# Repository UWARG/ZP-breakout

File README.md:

# ZP-breakout
Breakout Board for Zeropilot rev 1.0.

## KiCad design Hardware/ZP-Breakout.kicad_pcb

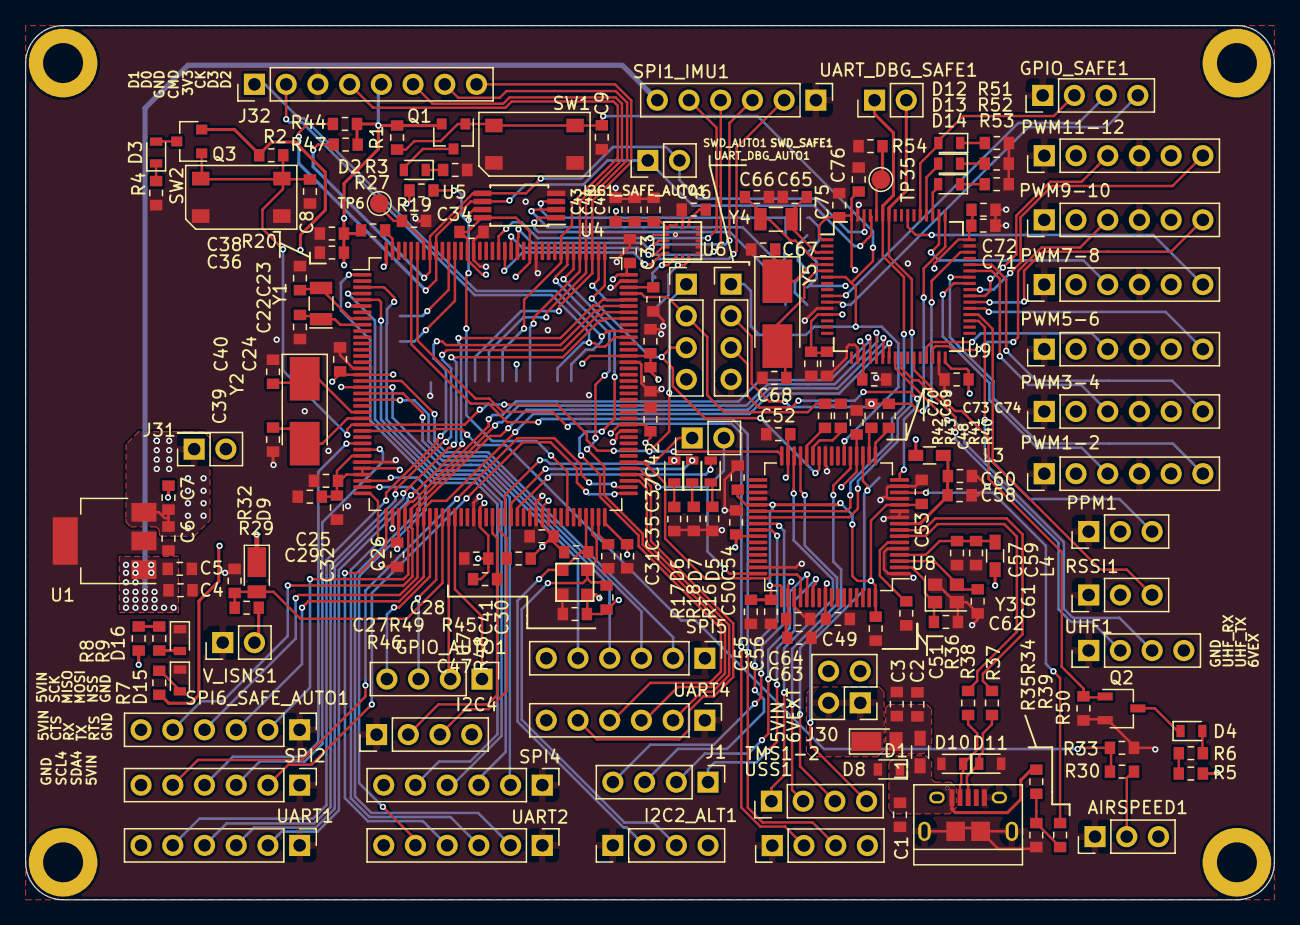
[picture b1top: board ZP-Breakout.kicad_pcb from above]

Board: 4 copper layers, 100.0 x 70.0 mm, 193 parts (0 on the bottom side), 160 nets.

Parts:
AIRSPEED1: GH-3; PinHeader_1x03_P2.54mm_Vertical
C1, C2, C43, C69: 10nF; C_0603_1608Metric_Pad0.84x1.00mm_HandSolder
C3, C4, C38, C59, C60, C63, C72, C76: 4.7uF; C_0603_1608Metric_Pad0.84x1.00mm_HandSolder
C5, C6, C32, C37, C70: 1uF; C_0603_1608Metric_Pad0.84x1.00mm_HandSolder
C7, C8, C9, C24, C25, C26, C27, C28, C29, C30, C31, C33, C34, C35, C36, C44, C46, C47, C48, C49, C50, C51, C52, C53, C54, C55, C57, C58, C64, C71, C73, C74, C75: 100nF; C_0603_1608Metric_Pad0.84x1.00mm_HandSolder
C22, C23, C65, C66: 14pF; C_0603_1608Metric_Pad0.84x1.00mm_HandSolder
C39, C40, C67, C68: 7pF; C_0603_1608Metric_Pad0.84x1.00mm_HandSolder
C41, C42, C45: 2.2uF; C_0603_1608Metric_Pad0.84x1.00mm_HandSolder
C56: 3.3uF; C_0603_1608Metric_Pad0.84x1.00mm_HandSolder
C61, C62: 8pF; C_0603_1608Metric_Pad0.84x1.00mm_HandSolder
D1, D10, D11: TVS; D_0603_1608Metric_Pad0.67x1.00mm_HandSolder
D2, D3, D5, D6, D7, D12, D13, D14: LED; LED_0603_1608Metric_Pad0.67x1.00mm_HandSolder
D4, D15, D16: PWR_LED; LED_0603_1608Metric_Pad0.67x1.00mm_HandSolder
D8, D9: D; D_PowerDI-123
GPIO_AUTO1: GH-4; PinHeader_1x04_P2.54mm_Vertical
GPIO_SAFE1: GH-4; PinHeader_1x04_P2.54mm_Vertical
H1, H2, H3, H4: MountingHole_M3; MountingHole_3.2mm_M3_ISO14580_Pad
I2C1_SAFE_AUTO1: GH-2; PinHeader_1x02_P2.54mm_Vertical
I2C2_ALT1, I2C4: GH-4; PinHeader_1x04_P2.54mm_Vertical
J1: GH-4; PinHeader_1x04_P2.54mm_Vertical
J8: Micro_SD_Card; micro_sd
J9: USB_MICRO_B; USB_Micro-B_10118194-0001LF
J30: Conn_02x02_Odd_Even; PinSocket_2x02_P2.54mm_Vertical
J31: Conn_01x02; PinSocket_2x01_P2.54mm_Vertical
J32: CONN-8; PinHeader_1x08_P2.54mm_Vertical
L1: BLM18PG221SN1D; L_0603_HandSoldering
L3, L4: 600R; L_0603_HandSoldering
PPM1: GH-3; PinHeader_1x03_P2.54mm_Vertical
PWM1-2, PWM3-4, PWM5-6, PWM7-8, PWM9-10, PWM11-12: GH-6; PinHeader_1x06_P2.54mm_Vertical
Q1, Q3: BSS84LT1G; SOT-23
Q2: BSS138; TSOT-23
R1, R2, R19, R22, R24, R26, R27, R35, R44, R45, R46, R47, R48, R49, R54: 10K; R_0603_1608Metric_Pad0.84x1.00mm_HandSolder
R3, R4, R5, R6, R7, R8, R9, R16, R17, R18, R51, R52, R53: 100; R_0603_1608Metric_Pad0.84x1.00mm_HandSolder
R20, R21, R23, R25, R41, R42: 0; R_0603_1608Metric_Pad0.84x1.00mm_HandSolder
R29: 150K; R_0603_1608Metric_Pad0.84x1.00mm_HandSolder
R30: 11K; R_0603_1608Metric_Pad0.84x1.00mm_HandSolder
R32, R33: 22K; R_0603_1608Metric_Pad0.84x1.00mm_HandSolder
R34: 4.7K; R_0603_1608Metric_Pad0.84x1.00mm_HandSolder
R36: 12K; R_0603_1608Metric_Pad0.84x1.00mm_HandSolder
R37, R38: 10; R_0603_1608Metric_Pad0.84x1.00mm_HandSolder
R39: 1K; R_0603_1608Metric_Pad0.84x1.00mm_HandSolder
R40, R43: 220; R_0603_1608Metric_Pad0.84x1.00mm_HandSolder
R50: 100K; R_0603_1608Metric_Pad0.84x1.00mm_HandSolder
RSSI1: GH-3; PinHeader_1x03_P2.54mm_Vertical
SPI1_IMU1, SPI2, SPI4, SPI5, SPI6_SAFE_AUTO1: GH-6; PinHeader_1x06_P2.54mm_Vertical
SW1, SW2: SW_Push_Dual_1-2short_3-4short; Button
SWD_AUTO1: GH-4; PinHeader_1x04_P2.54mm_Vertical
SWD_SAFE1: GH-4; PinHeader_1x04_P2.54mm_Vertical
TMS1-2: GH-4; PinHeader_1x04_P2.54mm_Vertical
TP1, TP2, TP3, TP4, TP5, TP6, TP35: TEST; TestPoint_Pad_D1.5mm
U1: MCP1826S-3302E/DB; SOT-223
U4: STM32F765ZGT6; LQFP-144_20x20mm_P0.5mm
U5: M24C64-WDW6TP; TSSOP-8_4.4x3mm_P0.65mm
U6: ICM-20602
U7: MS5637-02BA03
U8: FT4232H; LQFP-64_10x10mm_P0.5mm
U9: STM32F091RCT7; LQFP-64_10x10mm_P0.5mm
UART1, UART2, UART4: GH-6; PinHeader_1x06_P2.54mm_Vertical
UART_DBG_AUTO1: GH-2; PinHeader_1x02_P2.54mm_Vertical
UART_DBG_SAFE1: GH-2; PinHeader_1x02_P2.54mm_Vertical
UHF1: GH-4; PinHeader_1x04_P2.54mm_Vertical
USS1: GH-4; PinHeader_1x04_P2.54mm_Vertical
V_ISNS1: GH-2; PinHeader_1x02_P2.54mm_Vertical
Y1, Y4: 32.768kHz; Crystal_SMD_MicroCrystal_CC7V-T1A-2Pin_3.2x1.5mm
Y2, Y5: 8MHz; Crystal_SMD_5032-2Pin_5.0x3.2mm_HandSoldering
Y3: Crystal_GND24; Crystal_SMD_2520-4Pin_2.5x2.0mm

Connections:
/3V3: C24.1, C25.1, C26.1, C27.1, C28.1, C29.1, C30.1, C31.1, C32.2, C33.1, C34.1, C35.1, C36.1, C37.2, C38.2, C43.2, C44.1, C45.1, C47.2, C48.1, C49.1, C50.1, C52.1, C63.1, C64.1, C69.1, C70.1, C71.1, C72.1, C73.1, C74.1, C75.1, C76.1, D9.1, J8.4, J31.2, J32.5, L3.2, L4.2, Q1.2, Q3.2, R1.2, R2.2, R7.1, R20.1, R21.1, R23.1, R25.1, R27.1, R44.1, R45.1, R46.1, R47.1, R48.1, R49.1, U4.6, U4.17, U4.30, U4.32, U4.33, U4.39, U4.52, U4.62, U4.72, U4.84, U4.95, U4.108, U4.121, U4.131, U4.144, U5.8, U6.1, U6.16, U7.1, U8.20, U8.31, U8.42, U8.50, U8.56, U9.1, U9.13, U9.19, U9.32, U9.48, U9.64
/5V_INT: AIRSPEED1.3, C4.2, C5.1, I2C2_ALT1.4, I2C4.4, J30.4, R5.1, R8.1, SPI1_IMU1.6, SPI2.6, SPI4.6, SPI5.6, SPI6_SAFE_AUTO1.6, U1.1, UART1.6, UART2.6, UART4.6, USS1.4
/5V_USB: C1.2, D1.1, J9.1, L1.1, R34.1
/6V_EXT: J30.2, PWM1-2.2, PWM1-2.5, PWM3-4.2, PWM3-4.5, PWM5-6.2, PWM5-6.5, PWM7-8.2, PWM7-8.5, PWM9-10.2, PWM9-10.5, PWM11-12.2, PWM11-12.5, UHF1.4
/AIRSPD_ADC: R30.1, R33.1, U4.26
/AIR_SPD: AIRSPEED1.2, R30.2
/CTS1: U4.103, UART1.5
/CTS2: U4.34, UART2.5
/CTS4: U4.76, UART4.5
/JRST: TP5.1, U4.134
/MEMORY/E1: R21.2, R22.1, U5.1
/MEMORY/E2: R23.2, R24.1, U5.2
/MEMORY/E3: R25.2, R26.1, U5.3
/MEM_WC: R27.2, U4.66, U5.7
/MISO1: SPI1_IMU1.4, U4.124, U6.4
/MISO2: SPI2.4, U4.28
/MISO4: SPI4.4, U4.4
/MISO5: SPI5.4, U4.20
/MISO6: SPI6_SAFE_AUTO1.4, U4.42, U9.22
/MOSI1: SPI1_IMU1.3, U4.123, U6.3
/MOSI2: SPI2.3, U4.29
/MOSI4: SPI4.3, U4.5
/MOSI5: SPI5.3, U4.21
/MOSI6: SPI6_SAFE_AUTO1.3, U4.43, U9.23
/NRST_PILOT: C8.1, Q3.1, R2.1, SW2.1, SW2.2, SWD_AUTO1.1, U4.25, U8.32
/NRST_SAFETY: C9.1, Q1.1, R1.1, SW1.1, SW1.2, SWD_SAFE1.1, U8.22, U9.7
/NSS1: SPI1_IMU1.2, U4.125, U6.5
/NSS2: SPI2.2, U4.73
/NSS4: SPI4.2, U4.3
/NSS5: SPI5.2, U4.18
/NSS6: SPI6_SAFE_AUTO1.2, U4.40, U9.20
/PB1: GPIO_AUTO1.2, U4.47
/PB2: GPIO_AUTO1.1, U4.48
/PC4: GPIO_AUTO1.4, U4.44
/PC5: GPIO_AUTO1.3, U4.45
/POWER/3V3_JMP: C6.1, C7.1, J31.1, U1.3
/POWER/5V_INT_JMP: D8.1, J30.1, J30.3
/PPM: PPM1.3, U9.35
/PWM 1-12/PWM1: PWM1-2.3, U9.41
/PWM 1-12/PWM2: PWM1-2.6, U9.42
/PWM 1-12/PWM3: PWM3-4.3, U9.43
/PWM 1-12/PWM4: PWM3-4.6, U9.44
/PWM 1-12/PWM5: PWM5-6.3, U9.29
/PWM 1-12/PWM6: PWM5-6.6, U9.37
/PWM 1-12/PWM7: PWM7-8.3, U9.50
/PWM 1-12/PWM8: PWM7-8.6, U9.55
/PWM 1-12/PWM9: PWM9-10.3, U9.30
/PWM 1-12/PWM10: PWM9-10.6, U9.38
/PWM 1-12/PWM11: PWM11-12.3, U9.39
/PWM 1-12/PWM12: PWM11-12.6, U9.40
/RSSI: RSSI1.3, U9.36
/RTS1: U4.104, UART1.2
/RTS2: U4.35, UART2.2
/RTS4: U4.75, UART4.2
/RX1: U4.102, UART1.4
/RX2: U4.37, UART2.4
/RX3: U4.78, U8.52, UART_DBG_AUTO1.1
/RX4: U4.114, UART4.4
/SAFETY_DBG_RX: U8.38, U9.59, UART_DBG_SAFE1.1
/SAFETY_DBG_TX: U8.39, U9.58, UART_DBG_SAFE1.2
/SCK1: SPI1_IMU1.5, U4.126, U6.2
/SCK2: SPI2.5, U4.74
/SCK4: SPI4.5, U4.1
/SCK5: SPI5.5, U4.19
/SCK6: SPI6_SAFE_AUTO1.5, U4.41, U9.21
/SCL1: I2C1_SAFE_AUTO1.1, R44.2, U4.136, U5.6, U9.61
/SCL2: I2C2_ALT1.2, R45.2, U4.69, U7.3
/SCL4: I2C4.2, R46.2, U4.54
/SCLK_PILOT: SWD_AUTO1.3, U4.109, U8.26
/SCLK_SAFETY: SWD_SAFE1.3, U8.16, U9.49
/SDA1: I2C1_SAFE_AUTO1.2, R47.2, U4.137, U5.5, U9.62
/SDA2: I2C2_ALT1.3, R48.2, U4.70, U7.2
/SDA4: I2C4.3, R49.2, U4.55
/SD_CK: J8.5, J32.6, U4.113
/SD_CMD: J8.3, J32.4, U4.116
/SD_D0: J8.7, J32.2, U4.98
/SD_D1: J8.8, J32.1, U4.99
/SD_D2: J8.1, J32.8, U4.111
/SD_D3: J8.2, J32.7, U4.112
/SENSORS/IMU_FSYNC: TP2.1, U6.8
/SENSORS/IMU_INT: TP1.1, U6.6
/SWIO_PILOT: R42.2, R43.2, SWD_AUTO1.2, U4.105
/SWIO_SAFETY: R40.2, R41.2, SWD_SAFE1.2, U9.46
/S_PC2: GPIO_SAFE1.3, U9.10
/S_PC3: GPIO_SAFE1.4, U9.11
/S_PC12: D12.2, GPIO_SAFE1.2, U9.53
/TDI: TP3.1, U4.110
/TDO: TP4.1, U4.133
/TDO1_TST: TMS1-2.4, U8.19
/TDO2_TST: TMS1-2.2, U8.29
/TMS1_TST: TMS1-2.3, U8.21
/TMS2_TST: TMS1-2.1, U8.30
/TX1: U4.101, UART1.3
/TX2: U4.36, UART2.3
/TX3: U4.77, U8.48, UART_DBG_AUTO1.2
/TX4: U4.115, UART4.3
/UART1_CTS_TST: J1.3, U8.41
/UART1_RTS_TST: J1.4, U8.40
/UART2_CTS_TST: J1.1, U8.54
/UART2_RTS_TST: J1.2, U8.53
/UHF_RX: U9.25, UHF1.2
/UHF_TX: U9.24, UHF1.3
/ULTRA_SONIC_1: U4.139, USS1.2
/ULTRA_SONIC_2: U4.140, USS1.3
/USB Interface/D+: R37.1, U8.8
/USB Interface/D-: R38.1, U8.7
/USB Interface/DR+: D11.1, J9.3, R37.2
/USB Interface/DR-: D10.1, J9.2, R38.2
/V_ISENSE: R29.2, V_ISNS1.2
/V_ISENSE_ADC: D9.2, R29.1, R32.1, U4.46
GND: AIRSPEED1.1, C1.1, C2.1, C3.1, C4.1, C5.2, C6.2, C7.2, C8.2, C9.2, C22.2, C23.2, C24.2, C25.2, C26.2, C27.2, C28.2, C29.2, C30.2, C31.2, C32.1, C33.2, C34.2, C35.2, C36.2, C37.1, C38.1, C39.2, C40.2, C41.1, C42.1, C43.1, C44.2, C45.2, C46.2, C47.1, C48.2, C49.2, C50.2, C51.2, C52.2, C53.2, C54.2, C55.2, C56.2, C57.2, C58.2, C59.2, C60.2, C61.2, C62.2, C63.2, C64.2, C65.1, C66.1, C67.1, C68.1, C69.2, C70.2, C71.2, C72.2, C73.2, C74.2, C75.2, C76.2, D1.2, D10.2, D11.2, D15.1, D16.1, GPIO_SAFE1.1, I2C2_ALT1.1, I2C4.1, J8.6, J8.9, J9.5, J9.6, J32.3, PPM1.1, PWM1-2.1, PWM1-2.4, PWM3-4.1, PWM3-4.4, PWM5-6.1, PWM5-6.4, PWM7-8.1, PWM7-8.4, PWM9-10.1, PWM9-10.4, PWM11-12.1, PWM11-12.4, Q2.2, R3.2, R4.2, R16.2, R17.2, R18.2, R19.1, R22.2, R24.2, R26.2, R32.2, R33.2, R35.2, R36.2, R50.2, R51.2, R52.2, R53.2, R54.2, RSSI1.1, SPI1_IMU1.1, SPI2.1, SPI4.1, SPI5.1, SPI6_SAFE_AUTO1.1, SW1.3, SW1.4, SW2.3, SW2.4, SWD_AUTO1.4, SWD_SAFE1.4, U1.2, U1.4, U4.16, U4.31, U4.38, U4.51, U4.61, U4.83, U4.94, U4.107, U4.120, U4.130, U5.4, U6.9, U6.10, U6.11, U6.12, U6.13, U6.15, U7.4, U8.1, U8.5, U8.10, U8.11, U8.13, U8.15, U8.25, U8.35, U8.47, U8.51, U9.12, U9.18, U9.31, U9.47, U9.63, UART1.1, UART2.1, UART4.1, UHF1.1, USS1.1, V_ISNS1.1, Y3.2, Y3.4
unnamed: C2.2, C3.2, D8.2, L1.2
unnamed: C22.1, U4.9, Y1.1
unnamed: C23.1, U4.8, Y1.2
unnamed: C39.1, U4.24, Y2.2
unnamed: C40.1, U4.23, Y2.1
unnamed: C41.2, U4.71
unnamed: C42.2, U4.106
unnamed: C46.1, U6.14
unnamed: C51.1, C53.1, C54.1, C55.1, C56.1, U8.12, U8.37, U8.49, U8.64
unnamed: C57.1, C59.1, L4.1, U8.4
unnamed: C58.1, C60.1, L3.1, U8.9
unnamed: C61.1, U8.3, Y3.3
unnamed: C62.1, U8.2, Y3.1
unnamed: C65.2, U9.3, Y4.1
unnamed: C66.2, U9.4, Y4.2
unnamed: C67.2, U9.5, Y5.1
unnamed: C68.2, U9.6, Y5.2
unnamed: D2.1, R3.1
unnamed: D2.2, Q1.3
unnamed: D3.1, R4.1
unnamed: D3.2, Q3.3
unnamed: D4.1, Q2.3
unnamed: D4.2, R6.2
unnamed: D5.1, R16.1
unnamed: D5.2, U4.58
unnamed: D6.1, R17.1
unnamed: D6.2, U4.56
unnamed: D7.1, R18.1
unnamed: D7.2, U4.57
unnamed: D12.1, R51.1
unnamed: D13.1, R52.1
unnamed: D13.2, U9.52
unnamed: D14.1, R53.1
unnamed: D14.2, U9.51
unnamed: D15.2, R7.2
unnamed: D16.2, R9.2
unnamed: Q2.1, R50.1, U9.27
unnamed: R5.2, R6.1
unnamed: R8.2, R9.1
unnamed: R19.2, TP6.1, U4.138
unnamed: R20.2, U4.143
unnamed: R34.2, R35.1, R39.2
unnamed: R36.1, U8.6
unnamed: R39.1, U8.14
unnamed: R40.1, U8.17
unnamed: R41.1, U8.18
unnamed: R42.1, U8.28
unnamed: R43.1, U8.27
unnamed: R54.1, TP35.1, U9.60

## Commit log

2021-01-24 Schematic done, tentative placement
2021-02-01 Finished routing. TODO: Silk.
2021-02-02 Added additional headers to some interfaces, GPIOs, and FTDI pins. Added silks
2021-02-02 associated components to their JLC part numbers
